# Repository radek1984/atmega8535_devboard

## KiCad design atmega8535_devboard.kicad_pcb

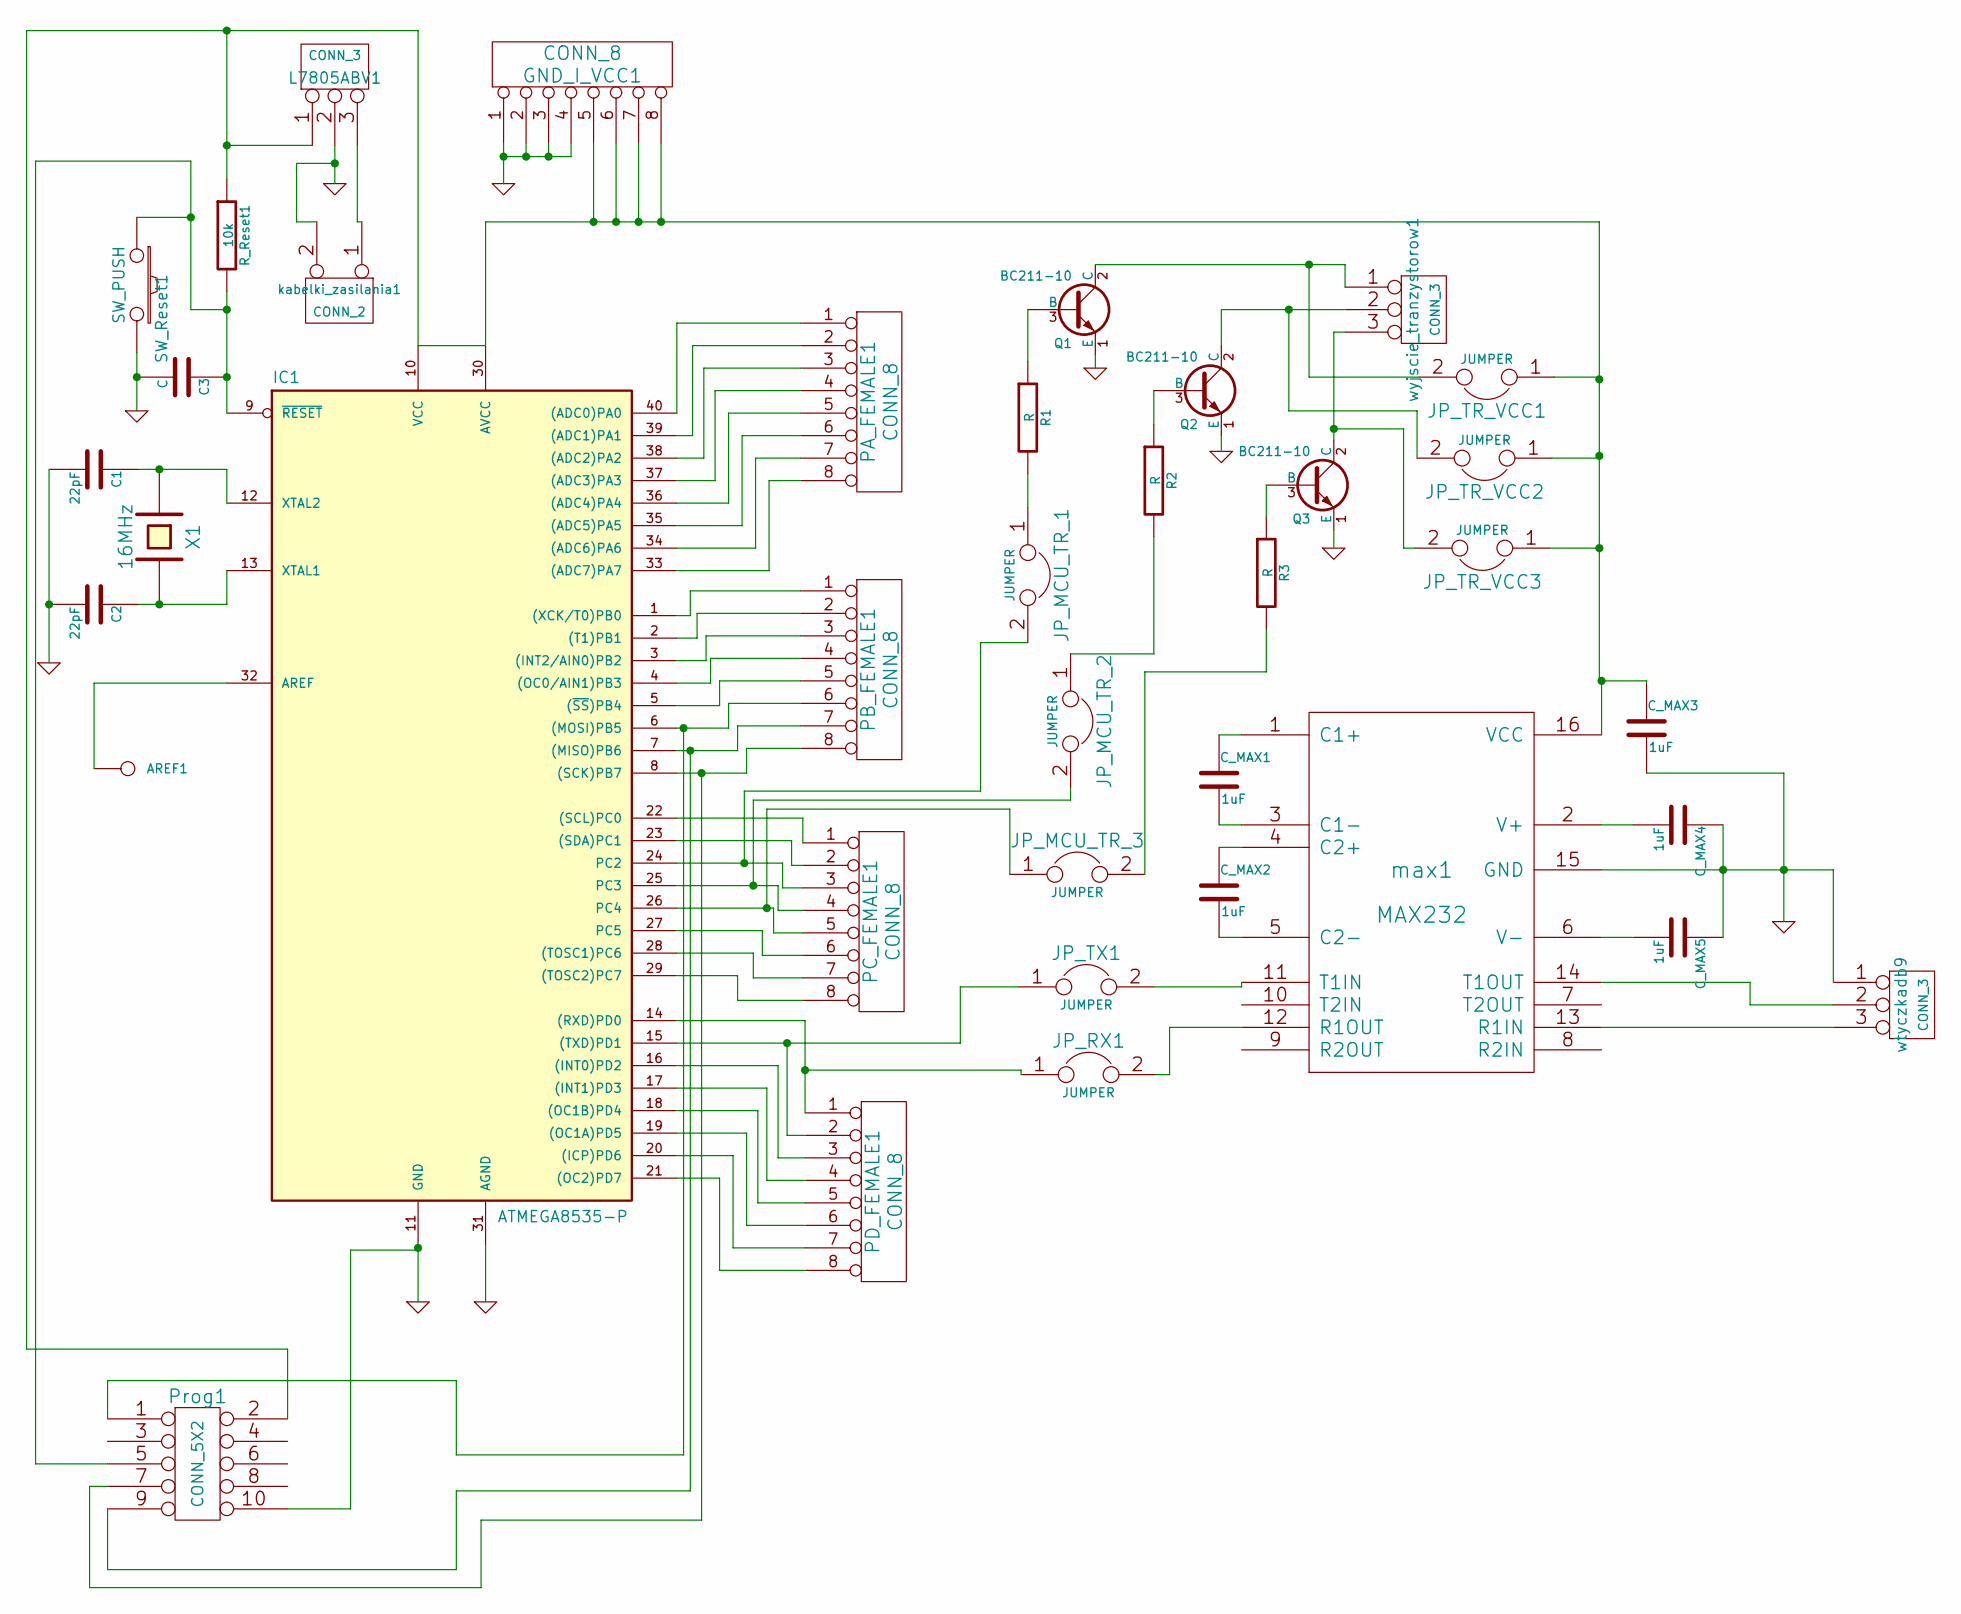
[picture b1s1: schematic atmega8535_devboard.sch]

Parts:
AREF1: CONN_1; 1pin
C1, C2: 22pF; C_Disc_D3.4mm_W2.1mm_P2.50mm
C3: C; C_Disc_D3.4mm_W2.1mm_P2.50mm
C_MAX1, C_MAX2, C_MAX3, C_MAX4, C_MAX5: 1uF; C_Disc_D5.0mm_W2.5mm_P2.50mm
GND_I_VCC1: CONN_8; TerminalBlock_Phoenix_MPT-2.54mm_8pol
IC1: ATMEGA8535-P; DIP-40_W15.24mm
JP_MCU_TR_1, JP_MCU_TR_2, JP_MCU_TR_3: JUMPER; SDL-102-X-XX_2x01
JP_RX1: JUMPER; SDL-102-X-XX_2x01
JP_TR_VCC1, JP_TR_VCC2, JP_TR_VCC3: JUMPER; SDL-102-X-XX_2x01
JP_TX1: JUMPER; SDL-102-X-XX_2x01
L7805ABV1: CONN_3; TerminalBlock_Phoenix_MPT-2.54mm_3pol
PA_FEMALE1: CONN_8; TerminalBlock_Phoenix_MPT-2.54mm_8pol
PB_FEMALE1: CONN_8; TerminalBlock_Phoenix_MPT-2.54mm_8pol
PC_FEMALE1: CONN_8; TerminalBlock_Phoenix_MPT-2.54mm_8pol
PD_FEMALE1: CONN_8; TerminalBlock_Phoenix_MPT-2.54mm_8pol
Prog1: CONN_5X2; SDL-110-X-XX_2x05
Q1, Q2, Q3: BC211-10; TO-92_Rugged
R1, R2, R3: R; R_Axial_DIN0207_L6.3mm_D2.5mm_P10.16mm_Horizontal
R_Reset1: 10k; R_Axial_DIN0207_L6.3mm_D2.5mm_P10.16mm_Horizontal
SW_Reset1: SW_PUSH; SW_PUSH_6mm
X1: 16MHz; Crystal_HC49-4H_Vertical
kabelki_zasilania1: CONN_2; TerminalBlock_Phoenix_MPT-2.54mm_2pol
max1: MAX232; DIP-16_W7.62mm
wtyczkadb9: CONN_3; TerminalBlock_Phoenix_MPT-2.54mm_3pol
wyjscie_tranzystorow1: CONN_3; TerminalBlock_Phoenix_MPT-2.54mm_3pol

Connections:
GND: C1.2, C2.2, C3.2, C_MAX3.2, C_MAX4.1, C_MAX5.1, GND_I_VCC1.1, GND_I_VCC1.2, GND_I_VCC1.3, GND_I_VCC1.4, IC1.11 (GND), IC1.31 (AGND), L7805ABV1.2 (PM), Prog1.10, Q1.1 (E), Q2.1 (E), Q3.1 (E), SW_Reset1.2, kabelki_zasilania1.2 (PM), max1.15 (GND), wtyczkadb9.1
unnamed: AREF1.1, IC1.32 (AREF)
unnamed: C1.1, IC1.12 (XTAL2), X1.1
unnamed: C2.1, IC1.13 (XTAL1), X1.2
unnamed: C3.1, IC1.9 (~RESET), Prog1.5, R_Reset1.2, SW_Reset1.1
unnamed: C_MAX1.1, max1.1 (C1+)
unnamed: C_MAX1.2, max1.3 (C1-)
unnamed: C_MAX2.1, max1.4 (C2+)
unnamed: C_MAX2.2, max1.5 (C2-)
unnamed: C_MAX3.1, max1.16 (VCC)
unnamed: C_MAX4.2, max1.2 (V+)
unnamed: C_MAX5.2, max1.6 (V-)
unnamed: GND_I_VCC1.5, GND_I_VCC1.6, GND_I_VCC1.7, GND_I_VCC1.8, IC1.10 (VCC), IC1.30 (AVCC), JP_TR_VCC1.1, JP_TR_VCC2.1, JP_TR_VCC3.1, L7805ABV1.1, Prog1.2, R_Reset1.1
unnamed: IC1.1 ((XCK/T0)PB0), PB_FEMALE1.1
unnamed: IC1.2 ((T1)PB1), PB_FEMALE1.2
unnamed: IC1.3 ((INT2/AIN0)PB2), PB_FEMALE1.3
unnamed: IC1.4 ((OC0/AIN1)PB3), PB_FEMALE1.4
unnamed: IC1.5 ((~SS~)PB4), PB_FEMALE1.5
unnamed: IC1.6 ((MOSI)PB5), PB_FEMALE1.6, Prog1.1
unnamed: IC1.7 ((MISO)PB6), PB_FEMALE1.7, Prog1.9
unnamed: IC1.8 ((SCK)PB7), PB_FEMALE1.8, Prog1.7
unnamed: IC1.14 ((RXD)PD0), JP_RX1.1, PD_FEMALE1.1
unnamed: IC1.15 ((TXD)PD1), JP_TX1.1, PD_FEMALE1.2
unnamed: IC1.16 ((INT0)PD2), PD_FEMALE1.3
unnamed: IC1.17 ((INT1)PD3), PD_FEMALE1.4
unnamed: IC1.18 ((OC1B)PD4), PD_FEMALE1.5
unnamed: IC1.19 ((OC1A)PD5), PD_FEMALE1.6
unnamed: IC1.20 ((ICP)PD6), PD_FEMALE1.7
unnamed: IC1.21 ((OC2)PD7), PD_FEMALE1.8
unnamed: IC1.22 ((SCL)PC0), PC_FEMALE1.1
unnamed: IC1.23 ((SDA)PC1), PC_FEMALE1.2
unnamed: IC1.24 (PC2), JP_MCU_TR_1.2, PC_FEMALE1.3
unnamed: IC1.25 (PC3), JP_MCU_TR_2.2, PC_FEMALE1.4
unnamed: IC1.26 (PC4), JP_MCU_TR_3.1, PC_FEMALE1.5
unnamed: IC1.27 (PC5), PC_FEMALE1.6
unnamed: IC1.28 ((TOSC1)PC6), PC_FEMALE1.7
unnamed: IC1.29 ((TOSC2)PC7), PC_FEMALE1.8
unnamed: IC1.33 ((ADC7)PA7), PA_FEMALE1.8
unnamed: IC1.34 ((ADC6)PA6), PA_FEMALE1.7
unnamed: IC1.35 ((ADC5)PA5), PA_FEMALE1.6
unnamed: IC1.36 ((ADC4)PA4), PA_FEMALE1.5
unnamed: IC1.37 ((ADC3)PA3), PA_FEMALE1.4
unnamed: IC1.38 ((ADC2)PA2), PA_FEMALE1.3
unnamed: IC1.39 ((ADC1)PA1), PA_FEMALE1.2
unnamed: IC1.40 ((ADC0)PA0), PA_FEMALE1.1
unnamed: JP_MCU_TR_1.1, R1.2
unnamed: JP_MCU_TR_2.1, R2.2
unnamed: JP_MCU_TR_3.2, R3.2
unnamed: JP_RX1.2, max1.12 (R1OUT)
unnamed: JP_TR_VCC1.2, Q1.2 (C), wyjscie_tranzystorow1.1
unnamed: JP_TR_VCC2.2, Q2.2 (C), wyjscie_tranzystorow1.2 (PM)
unnamed: JP_TR_VCC3.2, Q3.2 (C), wyjscie_tranzystorow1.3
unnamed: JP_TX1.2, max1.11 (T1IN)
unnamed: L7805ABV1.3, kabelki_zasilania1.1
unnamed: Q1.3 (B), R1.1
unnamed: Q2.3 (B), R2.1
unnamed: Q3.3 (B), R3.1
unnamed: max1.13 (R1IN), wtyczkadb9.3
unnamed: max1.14 (T1OUT), wtyczkadb9.2 (PM)

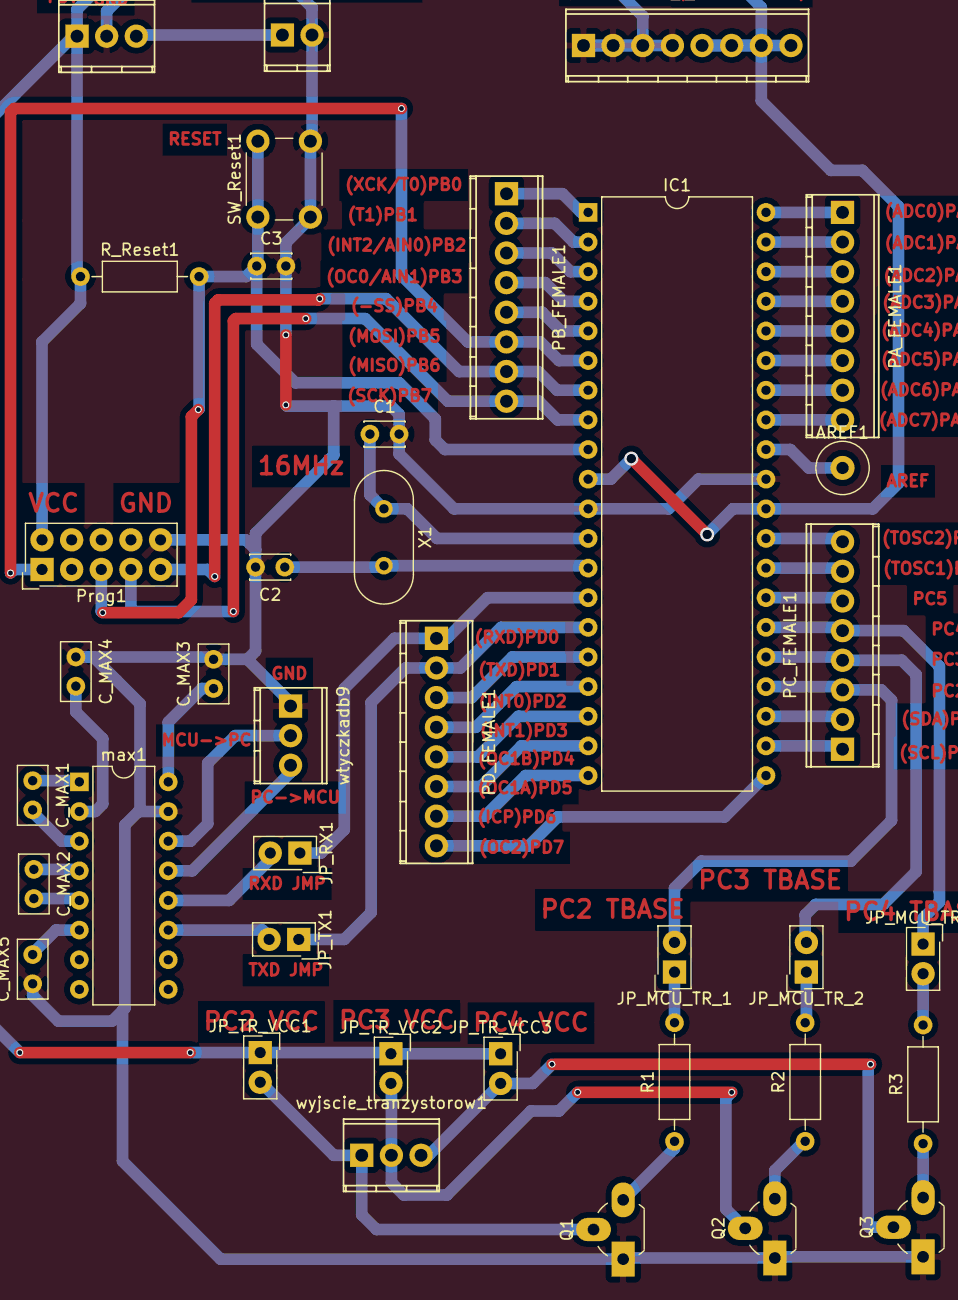
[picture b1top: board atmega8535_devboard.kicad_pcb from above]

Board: 2 copper layers, 38 parts (0 on the bottom side), 59 nets.

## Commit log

2018-12-05 make the board smaller
2018-12-06 add more ground
